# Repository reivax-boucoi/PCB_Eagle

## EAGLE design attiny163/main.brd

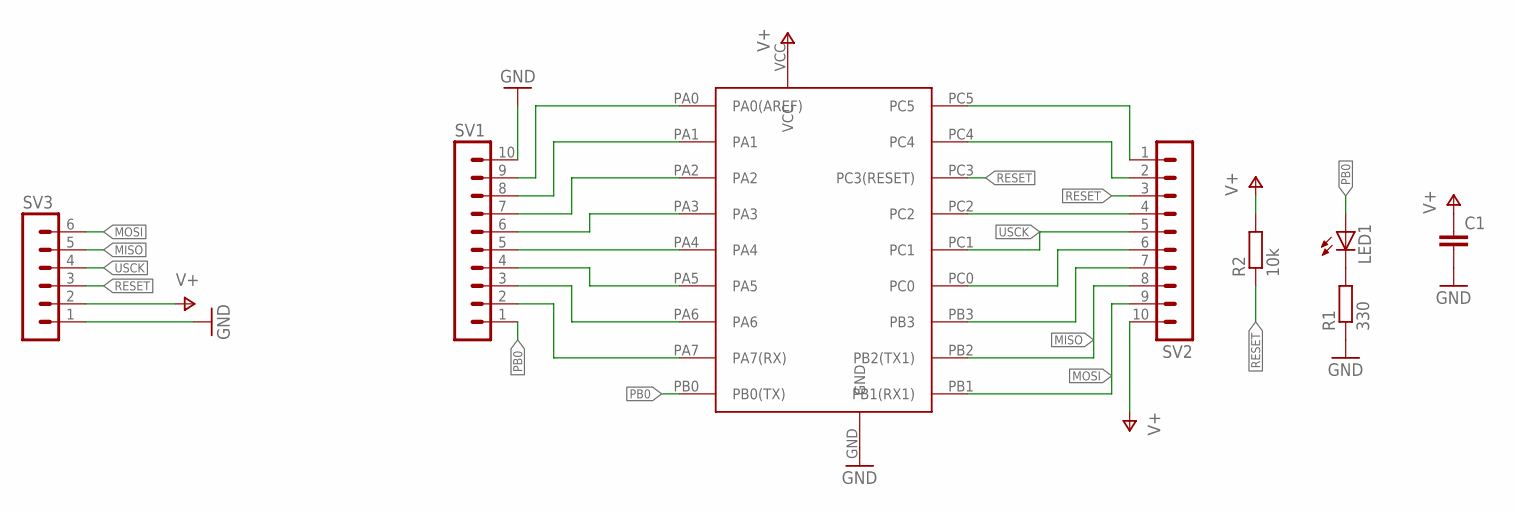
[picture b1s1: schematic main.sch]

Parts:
C1: CC0603; C0603
LED1: LEDCHIP-LED0603; CHIP-LED0603
R1: 330; R0603
R2: 10k; R0603
SV1, SV2: MA10-1
SV3: MA06-1
U$1: ATTINY1634; SOIC20

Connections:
GND: C1.2, R1.1, SV1.10, SV3.1, U$1.GND
MISO: SV2.8, SV3.5, U$1.PB2 (PB2(TX1))
MOSI: SV2.9, SV3.6, U$1.PB1 (PB1(RX1))
unnamed: LED1.C, R1.2
unnamed: SV2.1, U$1.PC5
unnamed: SV2.2, U$1.PC4
unnamed: SV1.9, U$1.PA0 (PA0(AREF))
unnamed: SV2.7, U$1.PB3
unnamed: SV2.6, U$1.PC0
unnamed: SV1.8, U$1.PA1
unnamed: SV1.7, U$1.PA2
unnamed: SV1.6, U$1.PA3
unnamed: SV1.5, U$1.PA4
unnamed: SV1.2, U$1.PA7 (PA7(RX))
unnamed: SV1.3, U$1.PA6
unnamed: SV1.4, U$1.PA5
unnamed: SV2.4, U$1.PC2
PB0: LED1.A, SV1.1, U$1.PB0 (PB0(TX))
RESET: R2.1, SV2.3, SV3.3, U$1.PC3 (PC3(RESET))
USCK: SV2.5, SV3.4, U$1.PC1
V+: C1.1, R2.2, SV2.10, SV3.2, U$1.VCC

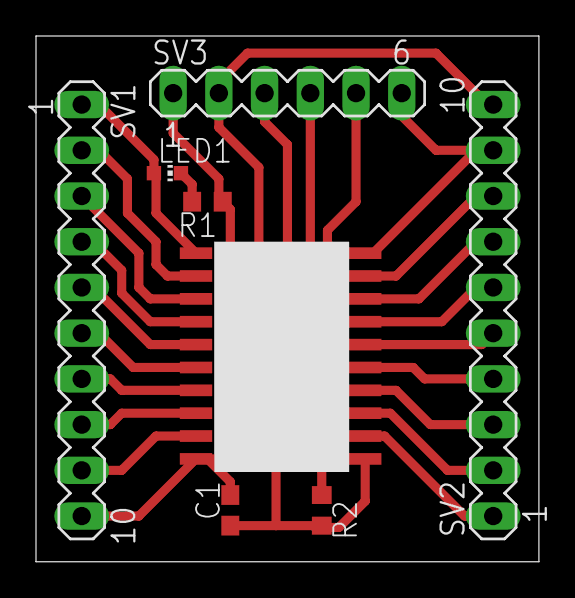
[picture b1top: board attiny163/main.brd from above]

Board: 2 copper layers, 27.9 x 29.2 mm, 8 parts (0 on the bottom side), 21 nets.

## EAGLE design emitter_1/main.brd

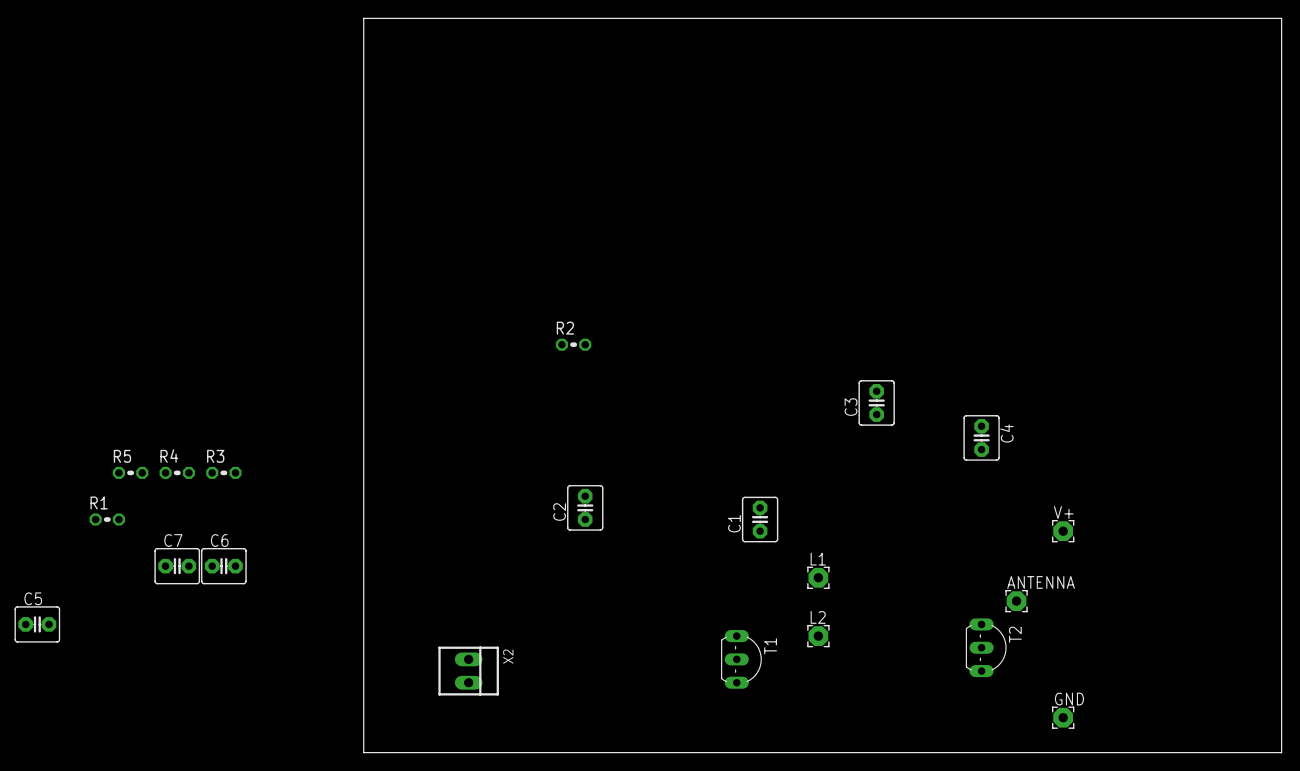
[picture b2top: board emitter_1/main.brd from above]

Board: 2 copper layers, 100.0 x 80.0 mm, 20 parts (0 on the bottom side), 8 nets, no tracks yet.

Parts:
ANTENNA: 2,15/1,0
C1, C2, C3, C4, C5, C6, C7: C2.5-4
GND: 2,15/1,0
L1, L2: 2,15/1,0
R1, R2, R3, R4, R5: 0204V
T1, T2: 2N2222; TO92-EBC-OVAL
V+: 2,15/1,0
X2: 22-23-2021

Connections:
unnamed: ANTENNA.1, C3.2, C4.1, C5.1, L2.1, T2.C
unnamed: C3.1, R1.2, T2.E
unnamed: C1.2, C2.2, R2.1, T2.B
unnamed: C2.1, C6.1, GND.1, R1.1, T1.E, X2.1
unnamed: C1.1, R3.1, R4.2, T1.C
unnamed: C7.1, R4.1, T1.B
unnamed: C7.2, R5.1, X2.2
unnamed: C4.2, C5.2, C6.2, L1.1, R2.2, R3.2, R5.2, V+.1

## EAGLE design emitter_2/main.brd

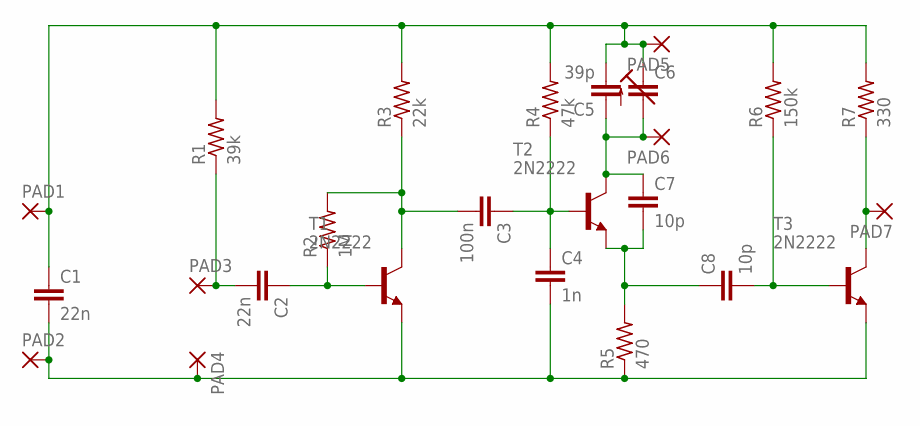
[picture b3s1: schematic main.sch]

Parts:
C1, C2: 22n; C2.5-2
C3: 100n; C2.5-2
C4: 1n; C2.5-2
C5: 39p; C2.5-2
C6: C-TRIMM3050.504; CTRIM3050.504
C7, C8: 10p; C2.5-2
PAD1, PAD2, PAD3, PAD4, PAD5, PAD6, PAD7: 2,54/0,8
R1: 39k; 0204V
R2: 1M; 0204V
R3: 22k; 0204V
R4: 47k; 0204V
R5: 470; 0204V
R6: 150k; 0204V
R7: 330; 0204V
T1, T2, T3: 2N2222; TO92-EBC-OVAL

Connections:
A: C5.1, C6.2 (A), C7.1, PAD6.1, T2.C
B: C2.2, PAD3.1, R1.1
C: C3.2, R2.2, R3.1, T1.C
D: C3.1, C4.1, R4.1, T2.B
E: C7.2, C8.1, R5.2, T2.E
F: PAD7.1, R7.1, T3.C
GND: C1.2, C4.2, PAD2.1, PAD4.1, R5.1, T1.E, T3.E
unnamed: C2.1, R2.1, T1.B
unnamed: C8.2, R6.1, T3.B
V+: C1.1, C5.2, C6.1 (E), PAD1.1, PAD5.1, R1.2, R3.2, R4.2, R6.2, R7.2

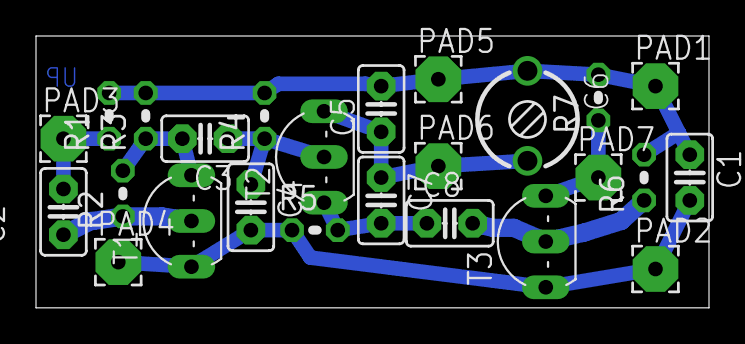
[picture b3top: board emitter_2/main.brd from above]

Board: 2 copper layers, 37.4 x 15.1 mm, 25 parts (0 on the bottom side), 10 nets.

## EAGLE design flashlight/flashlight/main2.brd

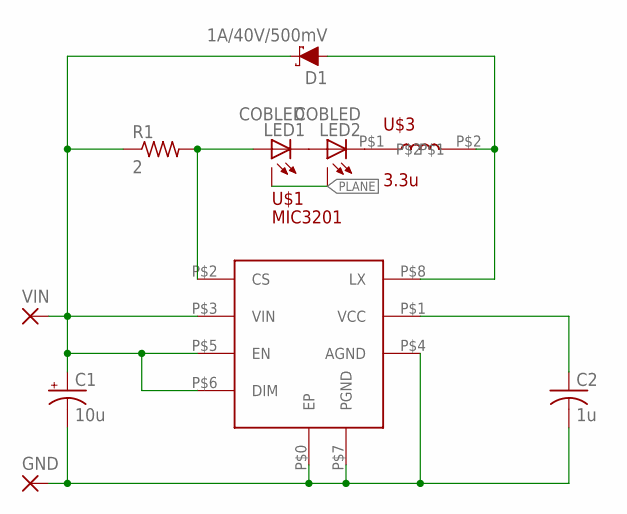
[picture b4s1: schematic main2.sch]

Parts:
C1: 10u; E2-5
C2: 1u; C0805
D1: 1A/40V/500mV; SMA-DIODE
GND: 2,54/1,0
LED1, LED2: COBLED
R1: 2; R0805
U$1: MIC3201; SOICNEP-8LD-LP-1
U$3: 3.3u; DO1813H
VIN: 2,54/1,0

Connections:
unnamed: LED1.P$2 (C), LED2.P$1 (A)
unnamed: C1.-, C2.2, GND.1, U$1.P$0 (EP), U$1.P$4 (AGND), U$1.P$7 (PGND)
unnamed: C1.+, D1.C, R1.1, U$1.P$3 (VIN), U$1.P$5 (EN), U$1.P$6 (DIM), VIN.1
unnamed: C2.1, U$1.P$1 (VCC)
unnamed: LED1.P$1 (A), R1.2, U$1.P$2 (CS)
unnamed: D1.A, U$1.P$8 (LX), U$3.P$2
unnamed: LED2.P$2 (C), U$3.P$1
PLANE: LED1.P$3 (A1), LED2.P$3 (A1)

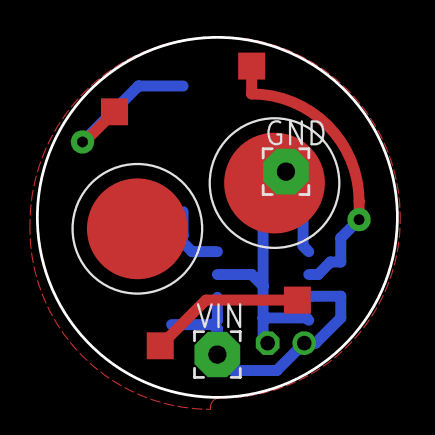
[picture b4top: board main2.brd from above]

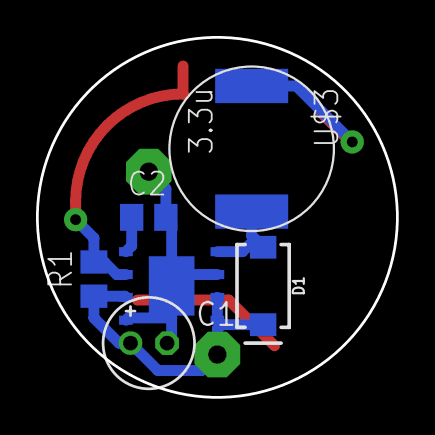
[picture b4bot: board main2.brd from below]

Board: 2 copper layers, 20.0 x 20.0 mm, 10 parts (6 on the bottom side), 8 nets.

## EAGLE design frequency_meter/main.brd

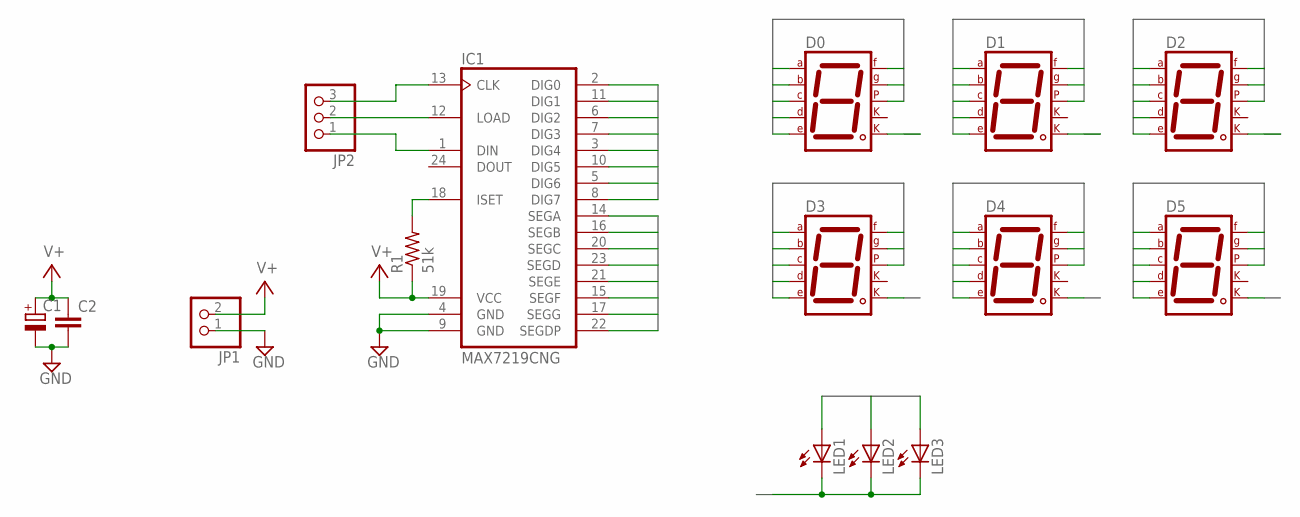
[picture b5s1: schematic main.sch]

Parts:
C1: CPOL-EUE2-5; E2-5
C2: C-EU050-025X075; C050-025X075
D0, D1, D2, D3, D4, D5: 7SEG-CK; 7SEG-13
IC1: MAX7219CNG; DIL24-3
JP1: PINHD-1X2; 1X02
JP2: PINHD-1X3; 1X03
LED1, LED2, LED3: LED3MM
R1: 51k; R0603

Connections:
DIG0: D0.8 (CK2), IC1.2 (DIG0)
DIG1: D1.8 (CK2), IC1.11 (DIG1)
DIG2: D2.8 (CK2), IC1.6 (DIG2)
DIG3: D3.8 (CK2), IC1.7 (DIG3)
DIG4: D4.8 (CK2), IC1.3 (DIG4)
DIG5: D5.8 (CK2), IC1.10 (DIG5)
DIG6: IC1.5 (DIG6), LED1.K (C), LED2.K (C), LED3.K (C)
DIG7: IC1.8 (DIG7)
GND: C1.-, C2.2, IC1.4 (GND), IC1.9 (GND), JP1.1
unnamed: IC1.18 (ISET), R1.2
unnamed: IC1.13 (CLK), JP2.3
unnamed: IC1.12 (LOAD), JP2.2
unnamed: IC1.1 (DIN), JP2.1
SEG0: D0.7 (A), D1.7 (A), D2.7 (A), D3.7 (A), D4.7 (A), D5.7 (A), IC1.14 (SEGA), LED1.A
SEG1: D0.6 (B), D1.6 (B), D2.6 (B), D3.6 (B), D4.6 (B), D5.6 (B), IC1.16 (SEGB), LED2.A
SEG2: D0.4 (C), D1.4 (C), D2.4 (C), D3.4 (C), D4.4 (C), D5.4 (C), IC1.20 (SEGC), LED3.A
SEG3: D0.2 (D), D1.2 (D), D2.2 (D), D3.2 (D), D4.2 (D), D5.2 (D), IC1.23 (SEGD)
SEG4: D0.1 (E), D1.1 (E), D2.1 (E), D3.1 (E), D4.1 (E), D5.1 (E), IC1.21 (SEGE)
SEG5: D0.9 (F), D1.9 (F), D2.9 (F), D3.9 (F), D4.9 (F), D5.9 (F), IC1.15 (SEGF)
SEG6: D0.10 (G), D1.10 (G), D2.10 (G), D3.10 (G), D4.10 (G), D5.10 (G), IC1.17 (SEGG)
SEG7: D0.5 (DP), D1.5 (DP), D2.5 (DP), D3.5 (DP), D4.5 (DP), D5.5 (DP), IC1.22 (SEGDP)
V+: C1.+, C2.1, IC1.19 (VCC), JP1.2, R1.1

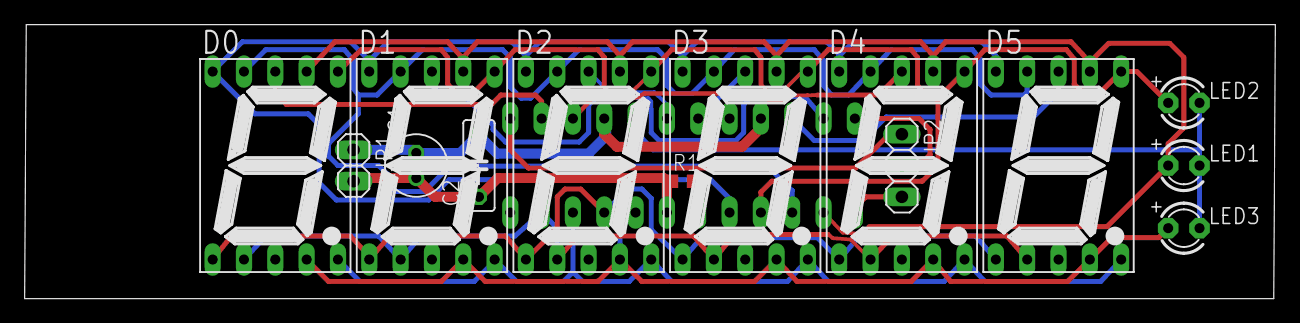
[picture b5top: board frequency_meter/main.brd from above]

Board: 2 copper layers, 101.4 x 22.2 mm, 15 parts (1 on the bottom side), 21 nets.

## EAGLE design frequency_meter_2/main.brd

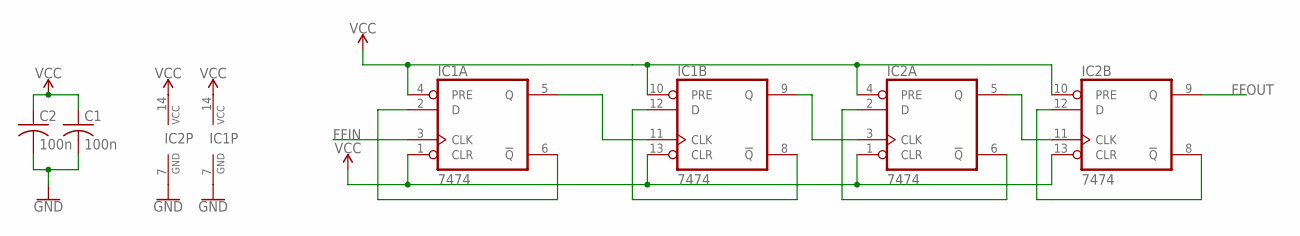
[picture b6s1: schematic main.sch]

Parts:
C1, C2: 100n; C0603
IC1, IC2: 7474; TSSOP14

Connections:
FFIN: IC1.3 (CLK)
FFOUT: IC2.9 (Q)
GND: C1.2, C2.2, IC1.7 (GND), IC2.7 (GND)
unnamed: IC1.5 (Q), IC1.11 (CLK)
unnamed: IC1.2 (D), IC1.6 (!Q)
unnamed: IC2.2 (D), IC2.6 (!Q)
unnamed: IC1.8 (!Q), IC1.12 (D)
unnamed: IC1.9 (Q), IC2.3 (CLK)
unnamed: IC2.5 (Q), IC2.11 (CLK)
unnamed: IC2.8 (!Q), IC2.12 (D)
VCC: C1.1, C2.1, IC1.1 (CLR), IC1.4 (PRE), IC1.10 (PRE), IC1.13 (CLR), IC1.14 (VCC), IC2.1 (CLR), IC2.4 (PRE), IC2.10 (PRE), IC2.13 (CLR), IC2.14 (VCC)

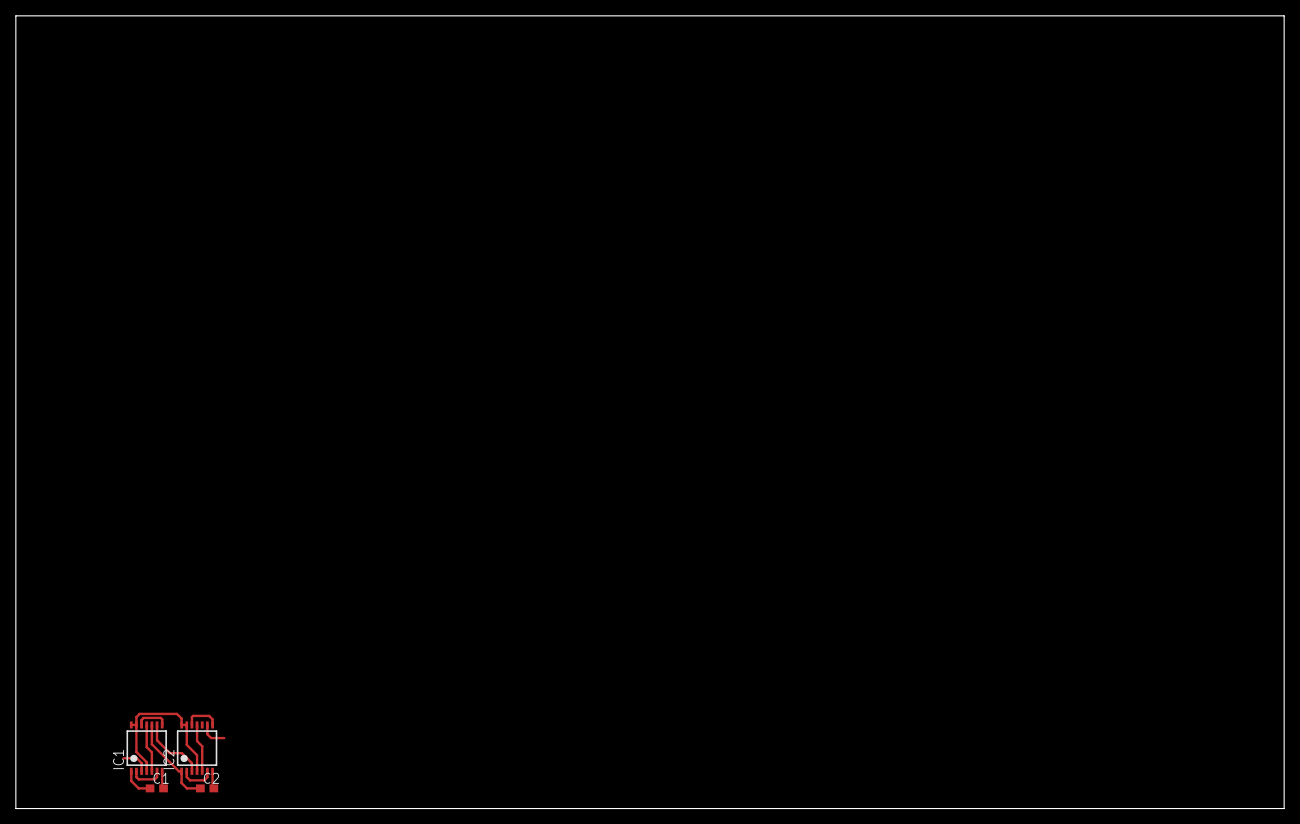
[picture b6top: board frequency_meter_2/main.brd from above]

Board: 2 copper layers, 160.0 x 100.0 mm, 4 parts (0 on the bottom side), 9 nets.

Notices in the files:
parts and their libraries:
SparkFun-DiscreteSemi: Licensing: Creative Commons ShareAlike 4.0 International - https://creativecommons.org/licenses/by-sa/4.0
